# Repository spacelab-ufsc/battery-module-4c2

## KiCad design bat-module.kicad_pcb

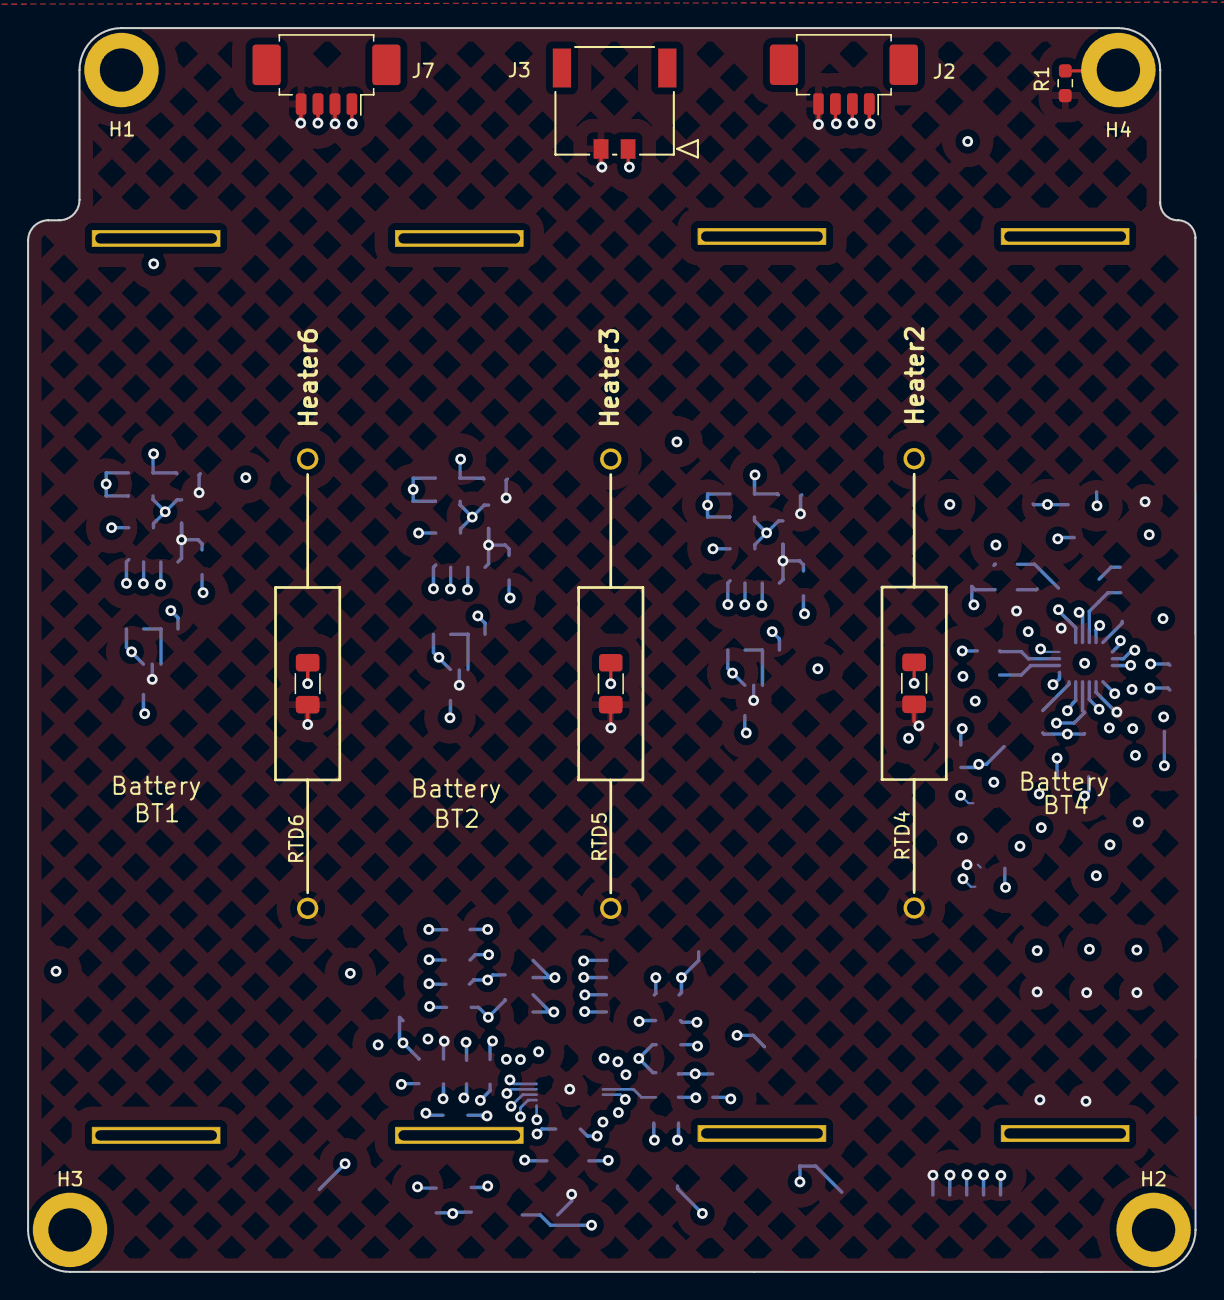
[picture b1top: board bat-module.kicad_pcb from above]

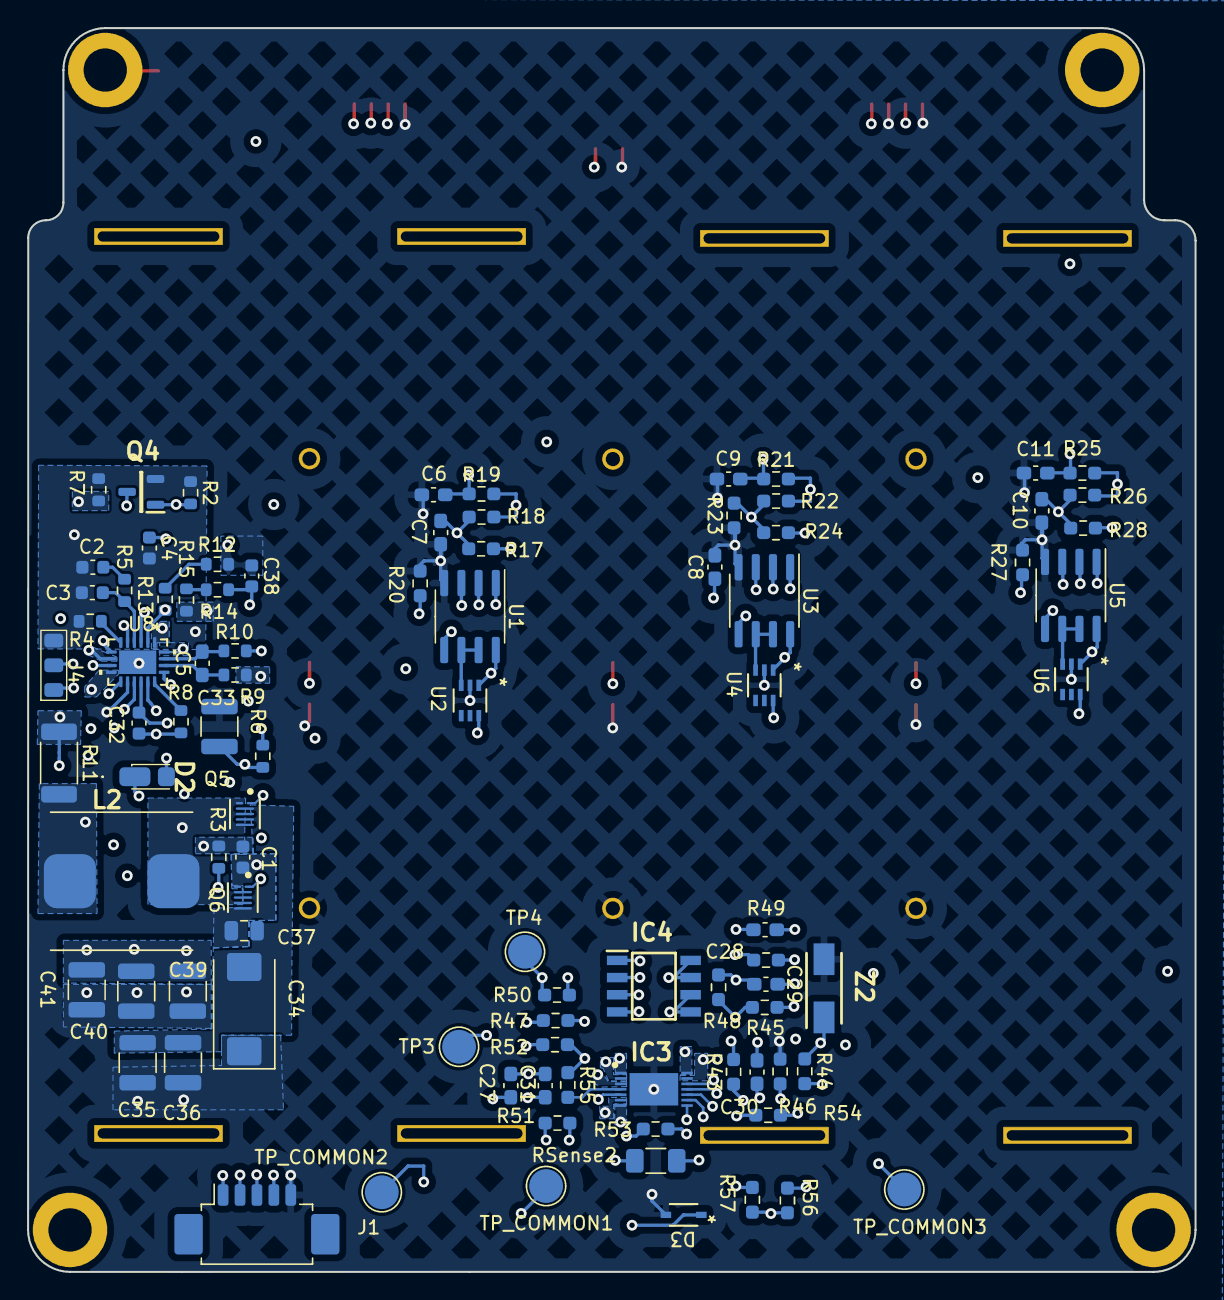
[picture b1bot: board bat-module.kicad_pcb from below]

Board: 4 copper layers, 86.3 x 91.9 mm, 110 parts (92 on the bottom side), 68 nets.

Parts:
BT1, BT2, BT3, BT4: Battery; BATTERY_18650_STRIP_CONTACT
C1, C32: 100nF; C0603C104K5RACTU
C2: 3.3nF; C0603C332J5GACAUTO
C3: 100pF; C0603C101J5GACAUTO
C4: 1nF; C0603C102F3GACTU
C5: 1nF; C_0603_1608Metric_Pad1.08x0.95mm_HandSolder
C6, C7, C8, C9, C10, C11: 100nF; C_0603_1608Metric_Pad1.08x0.95mm_HandSolder
C27, C31: 0.1uF/50V; C_0603_1608Metric_Pad1.08x0.95mm_HandSolder
C28, C29: 1000pF/50V; C_0603_1608Metric_Pad1.08x0.95mm_HandSolder
C30: 0.47uF/50V; C_0603_1608Metric_Pad1.08x0.95mm_HandSolder
C33: 4.7uF; GCM32ER71H475KA55L
C34: 47uF; T495X476K035ATE300
C35, C36: 10uF; C1210C106K5RACTU
C37: 1uF; C0805C105K5RACTU
C38: 22pF; C0603C220K5RACAUTO
C39, C40, C41: 22uF; GCM32ER71C226KE19L
D2: SS12FP
D3: D_Schottky_Filled; NSVR0320MW2T1G
H1, H2, H3: MountingHole; MountingHole_3.2mm_M3_ISO14580_Pad
H4: MountingHole_Pad; MountingHole_3.2mm_M3_ISO14580_Pad
Heater2, Heater3, Heater6: 20ppm/ ºC RS02B24R00FE12; RS02B24R00FE12
IC3: DS2777G+
IC4: FDS6898AZ
J1: Conn_01x05_Socket; Molex_PicoBlade_53261-0571_1x05-1MP_P1.25mm_Horizontal
J2, J7: Conn_01x04_Socket; Molex_PicoBlade_53261-0471_1x04-1MP_P1.25mm_Horizontal
J3: Conn_01x02_Socket; CON_2053380002
J4: 61300311121; three_position_jumper
JP2: SolderJumper_2_Bridged; Jumper
L2: 2.4uH; 744325240
Q4: SI2302DDS-T1-GE3
Q5, Q6: EPC2016C
R1: 1M; R_0603_1608Metric_Pad0.98x0.95mm_HandSolder
R2, R6: 100k; CRCW0603100KFKEAHP
R3: 2.2R; CRCW06032R20FKEAHP
R4: 82k; CRCW060382K0FKEA
R5: 12k; CRCW060312K0FKEAHP
R7, R12, R14: 0.0R; CRCW06030000Z0EAHP
R8, R9, R10: 10R; CRCW060310R0FKEAHP
R11: 8m; WSL20108L000FEA18
R13: 90.9k; CRCW060390K9FKEAHP
R15: 20k; CRCW060320K0FKEAHP
R17, R24, R28: 220k; R_0603_1608Metric_Pad0.98x0.95mm_HandSolder
R18, R19, R20, R21, R22, R23, R25, R26, R27: 10k; R_0603_1608Metric_Pad0.98x0.95mm_HandSolder
R43, R44, R52, R54: 150R; R_0603_1608Metric_Pad0.98x0.95mm_HandSolder
R45, R47, R50, R53, R55: 1K; R_0603_1608Metric_Pad0.98x0.95mm_HandSolder
R46, R48, R51: 0R; R_0603_1608Metric_Pad0.98x0.95mm_HandSolder
R49: 470R; R_0603_1608Metric_Pad0.98x0.95mm_HandSolder
R56, R57: 10K; R_0603_1608Metric_Pad0.98x0.95mm_HandSolder
RSense2: 0.01R/0.5W; R_1206_3216Metric_Pad1.30x1.75mm_HandSolder
RTD4, RTD5, RTD6: Thermistor; R_1206_3216Metric_Pad1.30x1.75mm_HandSolder
TP3: CC Test Point; TestPoint_Pad_D2.5mm
TP4: DC Test Point; TestPoint_Pad_D2.5mm
TP_COMMON1, TP_COMMON2, TP_COMMON3: TestPoint; TestPoint_Pad_D2.5mm
U1, U3, U5: LM358; SOIC-8_3.9x4.9mm_P1.27mm
U2, U4, U6: TPS22919QDCKRQ1
U8: LTC3833EUDC-TRPBF; LTC3833EUDC#TRPBF
Z2: 3SMAJ5919B-TP

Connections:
/bat-monitoring/+VBat: BT1.1, BT4.1, C29.2, IC4.7 (D2_1), IC4.8 (D2_2), R48.2, R52.1, R55.1, TP_COMMON2.1
/bat-monitoring/Bat2-: BT2.1, BT3.1, C27.1, C31.1, R51.2, TP_COMMON1.1
/bat-monitoring/I2C0_SCL: J1.3, R54.2, R56.2
/bat-monitoring/I2C0_SDA: J1.2, R43.1, R57.2
/bat-monitoring/PIO: J1.4, R44.1, Z2.1
/bat-monitoring/SRC: C30.1, IC3.13 (SRC), R49.2
/bat-monitoring/VBat_Common: BT1.1, BT2.1, BT3.1, BT4.1, R53.2, TP_COMMON3.1
/bat-monitoring/V_sense0_N: IC3.8 (SNS), R46.2, RSense2.1
/bat-monitoring/V_sense0_P: IC3.7 (VSS), R51.1, RSense2.2
/bat-monitoring/Veps+: C28.2, IC4.5 (D1_1), IC4.6 (D1_2), J3.1, R45.1, R48.1
/batteries/3V3: C38.1, C39.2, C40.2, C41.2, JP2.2 (B), R11.1, R12.1, R18.2, R19.2, R21.2, R22.2, R25.2, R26.2, R56.1, R57.1, U1.8 (V+), U2.1 (IN), U3.8 (V+), U4.1 (IN), U5.8 (V+), U6.1 (IN), U8.8 (EXTVCC), U8.20 (VOUT)
/batteries/3V3_A_~EN: J1.1, Q4.1 (G), R2.2
/batteries/3V3_SENSE1+: L2.2, R9.1, R11.2
/batteries/3V3_SENSE1-: JP2.1 (A), R10.1
/batteries/3V3_VCC1: C33.1, D2.2 (A), J4.1, R6.2, U8.9 (MODE/PLLIN), U8.11 (INTVCC)
/batteries/+VBatB: J7.1, J7.3, R3.2
/batteries/VBUS_BK3V3: C34.2 (ANODE), C35.1, C36.1, C37.1, Q5.3 (Drain), Q5.5 (Drain)
/heater-circuit/RTD2: C6.1, J2.1, R19.1, RTD4.2, U1.2 (-)
/heater-circuit/RTD3: C11.1, J2.2, R25.1, RTD5.2, U5.2 (-)
/heater-circuit/RTD6: C9.1, J2.3, R21.1, RTD6.2, U3.2 (-)
GNDREF: C1.1, C6.2, C7.2, C8.2, C9.2, C10.2, C11.2, C33.2, C34.1 (CATHODE), C35.2, C36.2, C37.2, C39.1, C40.1, C41.1, D3.2 (A), Heater2.2, Heater3.2, Heater6.2, IC3.15 (EP), J1.5, J2.4, J3.2, J7.2, J7.4, Q6.2 (Substrate), Q6.4 (Source), Q6.6 (Source), R1.2, R7.2, R15.1, R20.1, R23.1, R27.1, R46.1, RTD4.1, RTD5.1, RTD6.1, U1.4 (V-), U2.2 (GND), U3.4 (V-), U4.2 (GND), U5.4 (V-), U6.2 (GND), U8.1 (VOSNS-), U8.12 (PGND), Z2.2
GNDS: C2.2, C3.2, C4.2, J4.3, Q4.2 (S), R2.1, R4.1, R7.1, U8.21 (EPAD)
Heater_V2: Heater6.1, U2.6 (OUT)
Heater_V3: Heater3.1, U6.6 (OUT)
Heater_V6: Heater2.1, U4.6 (OUT)
unnamed: C2.1, R5.2
unnamed: C28.1, C29.1
unnamed: C32.1, D2.1 (K), R8.1
unnamed: D3.1 (K), IC3.10 (PLS), R45.2
unnamed: H4.1, R1.1
unnamed: IC3.1 (CC), R47.1
unnamed: C30.2, IC3.14 (CP)
unnamed: IC3.3 (DC), R50.2
unnamed: IC3.9 (PIO), R44.2
unnamed: IC3.12 (SCL/OVD), R54.1
unnamed: IC3.11 (SDA/DQ), R43.2
unnamed: C27.2, IC3.6 (VB)
unnamed: C31.2, IC3.2 (VDD), R52.2
unnamed: IC3.5 (VIN1), R53.1
unnamed: IC3.4 (VIN2), R55.2
unnamed: IC4.4 (G1), R47.2, TP3.1
unnamed: IC4.2 (G2), R50.1, TP4.1
unnamed: IC4.1 (S2), IC4.3 (S1), R49.1
unnamed: Q4.3 (D), U8.7 (RUN)
unnamed: Q5.1 (Gate), U8.15 (TG)
unnamed: C32.2, L2.1, Q5.2 (Substrate), Q5.4 (Source), Q5.6 (Source), Q6.3 (Drain), Q6.5 (Drain), U8.14 (SW)
unnamed: Q6.1 (Gate), U8.13 (BG)
unnamed: R12.2, R13.2
unnamed: R14.2, R15.2
unnamed: C7.1, R17.1, R18.1, R20.2, U1.3 (+)
unnamed: R17.2, U1.1, U1.5 (+)
unnamed: U1.6 (-), U1.7, U2.3 (ON)
unnamed: C8.1, R22.1, R23.2, R24.1, U3.3 (+)
unnamed: R24.2, U3.1, U3.5 (+)
unnamed: U3.6 (-), U3.7, U4.3 (ON)
unnamed: C10.1, R26.1, R27.2, R28.1, U5.3 (+)
unnamed: R28.2, U5.1, U5.5 (+)
unnamed: U5.6 (-), U5.7, U6.3 (ON)
unnamed: R8.2, U8.16 (BOOST)
unnamed: C3.1, R5.1, U8.4 (ITH)
unnamed: R6.1, U8.17 (PGOOD)
unnamed: R4.2, U8.6 (RT)
unnamed: C5.1, R9.2, U8.18 (SENSE+)
unnamed: C5.2, R10.2, U8.19 (SENSE-)
unnamed: C4.1, U8.3 (TRACK/SS)
unnamed: C1.2, R3.1, U8.10 (VIN)
unnamed: C38.2, R13.1, R14.1, U8.2 (VOSNS+)
unnamed: J4.2, U8.5 (VRNG)

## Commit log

2023-08-10 hardware: initial commit creating project and .sch #1
2023-08-11 hardware: importing board outline and holes positions #2
2023-08-11 hardware: adding initial project library
2023-08-11 hardware: reproducing eps2 schematics for battery monitoring
2023-08-16 hardware: moving main files
2023-08-16 hardware: updating library
2023-08-16 hardware: creating batteries circuit
2023-08-18 i2c-obdh connection and removing picoblade interface #3 #4
2023-08-18 organising files
2023-08-18 general fixes #3 #4
2023-09-05 updating lib
2023-09-05 developing rtd and heater circuits
2023-09-12 organizing library
2023-09-12 fixing voltages and uploading heater circuit
2023-09-14 Creating hierarquical labels and organizing root
2023-10-09 general improvements in schematics
2023-10-09 updating project library
2023-10-09 preliminar model layout
2023-11-15 fixing tracks and zones in DS2777G+
2023-11-16 retracing trails, changing footprints and improving circuit
2023-11-20 trying to fix drc comments
2023-11-20 changing footprints and 3ds
2024-03-04 changing edge cuts and other fixes
